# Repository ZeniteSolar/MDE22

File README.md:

# Electric Steering for Solar Boat

Instituto Federal de Educação, Ciência e Tecnologia de Santa Catarina - Campus Florianópolis

Electronics Academic Department

Degree in Electronics Engineering

Course: Integrative Project III

Professors:

* Robinson Pizzio and Daniel Lohmann

Student:

* Gabriel Ayres Rodrigues

# Summary

1. [Introduction](#introduction)
2. [Conception](#conception)
3. [Design](#design)
4. [Implementation](#implementation)
5. [Operation](#operation)
6. [Considerations](#considerations)
7. [References](#references)

# Introduction

This module aims to control the direction of the tail of the Guarapuvu II vessel, belonging to the IFSC Zênite Solar team.

It is inspired by the previously implemented system, developed by Cesar Dias Parente. The project files can be found [here](https://github.com/ZeniteSolar/MDE18/tree/main).

The Zênite team vessel is operated in solar boat competitions, where high performance and robustness are required. Being the only boat to use electric steering on the competition's context, the team counts on a more reliable system and is able to outmaneuver competition, which is a significant advantage on the Slalom race

The current electronic system was damaged after the competition in March 2022, which is a motivator for its upgrade.

# Conception

Thinking about a steering system, choosing to use an electric steering can bring greater responsiveness even though it has a fraction of the weight of a mechanical system. In addition, mechanical systems can require physical effort from the driver and a greater need for maintenance. 

Below is the diagram representing an electric steering system and its parts.

Taking into account the above elements, the following problems must be confronted:
- Electronic systems in vehicles must have high robustness due to the vibrations to which they are exposed. In the case of high speed vessels, especially for marine operations, impacts are a big problem (besides oxidation of the circuits).
- As the target vehicle is used in competitions whose focus, and therefore the challenge, is on energy generation and consumption, the solution must be as efficient as possible to ensure the success of the team.
- A competitive environment between vehicles requires high performance from this equipment, not only to achieve victory but to ensure everyone's safety. Therefore, the functionality must be met as well as the other parameters.

To implement the whole, it is necessary to define the requirements of the parts, and the possible proposals to satisfy them.

* ## Sensors

There are some options for rotation sensors such as: inductive, optical, Hall effect sensor, rotation potentiometer, encoder. The most economical and simple-to-implement alternative is a common linear potentiometer, currently used in the Zênite team system.

The most used types for steering sensors on the market are the following: resistive, encoders, and those with GMR technology ([Giant magnetoresistance](https://en.wikipedia.org/wiki/Giant_magnetoresistance)). (see the companies considered in [References](#references))

Sensors of this level are state-of-the-art and therefore out of the question, however it is worth noting that the resistive sensor is still being used (even in common vehicles, such as the [butterfly position sensor](https://www.dpk.com.br/como-funciona-o-sensor-de-posicao-da-borboleta/)).

For a contrast between the leaders: resistive sensors have a disadvantage due to wear and possible poor contact, GMR can suffer interference in environments with a strong magnetic field, and encoders (because they are digital) present a challenge in the trade-off Precision X Complexity (thus, price).

Seeking the balance between robustness, ease of implementation and price, the resistive sensor stands out.
 
* ## Controller

The implemented CAN network eliminates the need for cabling with analog signal between the stern and the bow. This ensures noise reduction in sensor readings and takes advantage of existing CAN cabling, compacting the system.

In addition, communication over the network makes it possible for the module to send data and control the direction using messages from other modules. In this way, the range is open for future implementations that may include:

	Redundancy messages and/or sensors
	Low Power Mode - Enabled by the Data Processing Module
	remote steering

A commercial line microcontroller will be enough to guarantee the execution of the desired tasks and response time. In addition to PWM ports and ADC inputs, a microcontroller with a CAN interface like the STM32F103xx or equivalent would be interesting. However, this alternative exceeds the price of IC's transceiver and CAN interface, in addition its programming is more laborious.

Due to its ease of programming and price, the [ATmega328P](https://br.mouser.com/ProductDetail/Microchip-Technology-Atmel/ATMEGA328P-PU?qs=K8BHR703ZXguOQv3sKbWcg%3D%3D) is proposed. For the connection to the CAN network, the most common and affordable IC's are the transceiver
[MCP2551](https://br.mouser.com/datasheet/2/268/20001667G-1115479.pdf) and the CAN/SPI interface circuit [MCP2515](https://br.mouser.com/datasheet/ 2/268/MCP2515_Family_Data_Sheet_DS20001801K-2303489.pdf).

The steering wheel potentiometer reading function will be performed by another module already present in the bow: [MIC19](https://github.com/ZeniteSolar/MIC19)

* ## Power Circuit

The brushed DC motor is driven by an H bridge, currently powered by a 12V battery. The current circuit is implemented by two half-bridge integrated [BTS7960](https://pdf1.alldatasheet.com/datasheet-pdf/view/152657/INFINEON/BTS7960.html).

This component was discontinued, and the best alternative found was [FAN7093](https://www.mouser.com/datasheet/2/149/FAN7093-76982.pdf). As the current one is already in hand and this project is focused on integration and telemetry, the same integrated circuit was used.

* ## Measurements and Feedback

It is essential to provide the CAN network with data on power consumption, as it is a battery-powered power system. Therefore, a current sensor is proposed for each arm of the H-bridge.

Conveniently, the BTS7960 half-bridge integrated circuit has an output pin for current sensing — a current source is connected to the output, and the current IS is proportional to the load current IL according to the measuring resistor RIS.

Alternatively, a circuit like the [INA240](https://www.ti.com/lit/ds/symlink/ina240.pdf?ts=1649772128538) ultra-precise bidirectional current sensor with PWM rejection could be used. From the same family of IC's, the INA826 will be used to measure battery voltage (Hbridge voltage).

These measurements should contribute to the feedback, which will also have the tail position data. Bringing this data to a display ensures that the pilot is aware of the state of the system and the consumption that his riding is causing.

# Design

The module was developed with Kicad software, the project is in the hardware folder of this git and its complete schematic can be viewed [here](https://github.com/ayresgit/Modulo-Direcao-Eletrica/blob/main/hardware/ PDF/steeringmodule.pdf). Below is the general schematic:

The components chosen from the design analysis are the following: Linear Potentiometers, Atmega328P, BTS7960, MCP2515, MCP2551 (or MCP2561), and INA826.

To conform to the vessel's system modules, the following components will also be required:

	2 female RJ45 connectors,
	2 2-way 2EDGRC female terminal (robust and practical, alternative is to use terminal block),
	28-pin stamped socket for the atmega328p,
	zener diodes to protect the microcontroller's ADC,
	2 oscillator crystals

The Kicad software has a function to export a complete list of materials (BOM - Bill Of Materials). It can be found in the hardware folder, at this [link](https://github.com/ZeniteSolar/MDE22/blob/f59e0732b5ff4f93045a860adb85f9820dcc4e83/hardware/steeringmodule.csv).

Right ahead is the PCB 3D preview. As will be explained in the implementation stage, the PCB was made with the help of a milling machine from the institution.

| Front | Back |
| -----  | ----- |
|||

It is worth noting that this repository has an exclusive branch for an ordered board, whose layout was improved and the silkscreen was properly designed to assist in the Implementation stage and possible repairs. This board was not used during the project due to its delivery date.

| Ordered Front | Ordered Back |
| -----  | ----- |
|||

# Implementation

### PCB manufacturing

The PCB was made by DAELN's CNC milling machine, operated by the department's technicians, the result is shown below. As the manufactured PCB did not have the desired minimum spacing for the power grid, a grinder was used to exclude unwanted tracks — it is important to remember that this type of tool requires the use of PPE.

| Dremel Adjustments | PPE |
| --- | --- |
||

The board was tinned to protect the circuit against oxidation, and the pathways were made with wires from network cable, cut to size and then soldered in place.

From the order of the components, the soldering was done as follows: SMD, CI, Through-hole connectors being the last ones (to avoid physical stress on the board).

After work on the board, the conclusion was reached that the H-bridge ICs must come before the SMD. This change is interesting because the model needs to be welded with heat, in this case with the aid of a heat gun. The soldered PCB can be seen in the figure.

| Front | Back |
|:-----:|:-----:|
|||

Once the preparation processes are finished, the microcontroller programming begins, which is done in the C language. The libraries used and the source code can be found in the firmware folder of this repository.

# Operation

The operation stage is divided into two parts: Programming and bench tests. Starting with the basic logic, such as which microcontroller peripherals are used, these steps develop together.

#### Programming

Throughout the process, the microchip datasheet for the atmega328p was used as a reference, which can be found in the [References](#references) of this work.

In the configuration of the peripherals, starting with the ADC, a dilemma was found about the orientation of the system potentiometers. As the system is being upgraded, the current configuration was discarded. It is then defined that the developed code presupposes the following relationships:

| Potentiometer | Tail position |
| ------------- | ------------------- |
| Maximum value | starboard boundary |
| Average value | centered |
| Minimum value | port limit |

- ADC

The mechanical system that couples the DC motor to the rotation reading potentiometer has a limit close to 270°. The ability to maneuver over 90° to either side has proven useful in the past.
With that in mind, and considering that extreme precision is not required in controlling this angle, the 8-bit ADC is sufficient for all four channels:

- voltage sensor
- current sensor 1 and 2
- Rotation sensor

Each one is configured by the coefficients in adc.c, just operate some measures with unitary coefficients and then do the calculation.

$$ coefficient = {DesiredValue \over ObtainedValue} $$
    
It is interesting to do this test with the full scale value, as the "Desired Value" is naturally known.

- CAN network

Working with the CAN library: the CAN network is implemented from ID's, identifying the modules on the bus and their messages. To generate these IDs, the Zênite team developed a script that generates these values for the module under development.

This path also brings security, ensuring that there will be no equal identities or other conflicts caused by human error and/or parallel development. All of these can be found in the [CAN_IDS](https://github.com/ZeniteSolar/CAN_IDS) repository.

Having the ID's generated for the module and its messages, it is necessary to change the can_filter.h to include the ID's of who you want to listen to (in this case, this project needs to listen to [MIC19](https://github.com/ZeniteSolar/MIC19 )), and create the request and message sending functions in can_app.c/h.

- PWM

Some key points for PWM operation: Chosen timer, prescaler (desired frequency), duty cycle definition (in this case implemented by the set_pwm function in hbridge.c).

Due to an error in the Design stage, the PWM outputs are connected to the ATmega328P's basic timer pins, Timer/Counter 0. The timer's operating mode must be phase correct PWM (which guarantees greater synchronization in relation to Fast PWM). As described in the datasheet, the frequency can be calculated as follows:

$$ fOCnxPWM = {fclkI/O \over {N * 510}} $$

	fOCnxPWM is the PWM frequency on the OCnx ports (in the case of OC0A and OC0B, in PD5 and PD6)
	fclkI/O is the crystal oscillator clock frequency (16MHz)
	N is the configured prescaler

This timer has fewer bits and less functionality compared to the other two. For the application, the only impact was the use of a lower frequency than desired (~3921.5Hz). This happens due to the lack of prescaler options in Timer/Counter0:
    
	prescaler = 1, fPWM = 31.37kHz (exceeds half-bridge IC limits)
	prescaler = 8 --> 3.92kHz (used, suboptimal)

#### Circuit Tests

The bench tests were carried out with the aid of different voltage sources, in the laboratories of the IFSC campus Florianópolis.

<p align="center">

The ADC and CAN network tests were carried out, these results were displayed on the computer by serial communication connecting an arduino to the board's Usart bus.

In the case of PWM, it is necessary to use an oscilloscope, so the figures for some of the tests carried out with the aid of a rheostat are left.

| Duty Cycle 40% Signal | Duty Cycle 40% Values |
| ------ | ------ |
|||

| Duty Cycle 80% | Duty Cycle 80% Values |
| ------ | ------ |
|||

To test the circuit with high current, the resistance in the rheostat was reduced and the duty cycle was maintained:
| Duty Cycle 80% 3A  | Duty Cycle 80% Valores |
| ------ | ------ |
|||

These results were satisfactory, considering that the circuit was not accumulating heat, the PWM was in accordance with what was desired from the configuration, and the values according to the datasheet.

#### Tests with Engine

The next step is the engine test. Bench test setup is done on the vessel, with bench supplies, boards and necessary connections.

<p align="center">

During the motor test, operating logics were implemented to the PWM of the H-bridge:

	H bridge activated by the difference between the potentiometers
	centered start
	Forced center if there is no communication
	Reverse side protection

The last logic was considered interesting considering that the system itself is assembled/disassembled for trips to competitions or testing sites.

The mechanical part can be seen in the figure below. The transmission shaft is coupled to the belt by the disc, and the DC steering motor controls the belt.
At the top of this can be seen the potentiometer used to measure rotation.

<p align="center">

The engine tests were a success using the bench sources, the operation video is in the Images folder. Due to the file size github cannot run it so it needs to be downloaded. An alternative is to use this [drive link](https://drive.google.com/file/d/12XCSZ1QREOxFkqlZAvMiaMpx_ZMUlxNi/view?usp=sharing).

During the test powered by the 12V battery, the system stopped working. The lack of capacitance for the input voltage caused a failure in one of the half-bridge ICs, after replacing the IC and correcting the values in the schematic the system is safe and operational.

# Considerations

All microcontroller peripherals are functional. All electrical measurements, which were one of the main objectives, showed satisfactory accuracy.

The essential logic of operation is complete, there are safety locks and finally the engine can be controlled smoothly.

Component performance: satisfactory.

Plate manufacturing: poor result, manufacturing caused more work and compromised the robustness of the system. To correctly meet the objective of a more robust system, the PCB ordered must be used.

Below we can see the system assembled with an experimental support — due to the dimensions of the board, a support dedicated to it needs to be manufactured.

On the side, the main power supply module ([MFP19](https://github.com/ZeniteSolar/MFP19)) is shown, which converts the voltage in the battery bank and supplies 18V from the CAN network. Future boat supports are expected to follow this 3D-printed model.

| Assembled System | Support Example |
| --- | --- |
|||

For comparison, here are screenshots of the previous system.

| Previous System | H Bridge |
| --- | --- |
|||

#### Next steps

Some of the next steps for this module and future updates:

- PWM responsive to pilot movements
- H-Bridge design or choice of non-discontinued IC
- Redundancy messages and/or sensors
- Low power mode - Activated by data processing module
- *Remote steering

*The success of this step would make room for a fascinating update: The Autonomous Boat.

# References

Datasheet ATmega328P:
[Microchip, Atmel ATmega328P](https://ww1.microchip.com/downloads/en/DeviceDoc/Atmel-7810-Automotive-Microcontrollers-ATmega328P_Datasheet.pdf)

Steering sensor market research:
[Bosch](https://www.bosch-motorsport.com/content/downloads/Raceparts/en-GB/120530059.html),
[CUI Inc](https://www.cuidevices.com/catalog/motion/rotary-encoders),
[TT Electronics](https://www.ttelectronics.com/products/categories/steering-sensors/search-results/)

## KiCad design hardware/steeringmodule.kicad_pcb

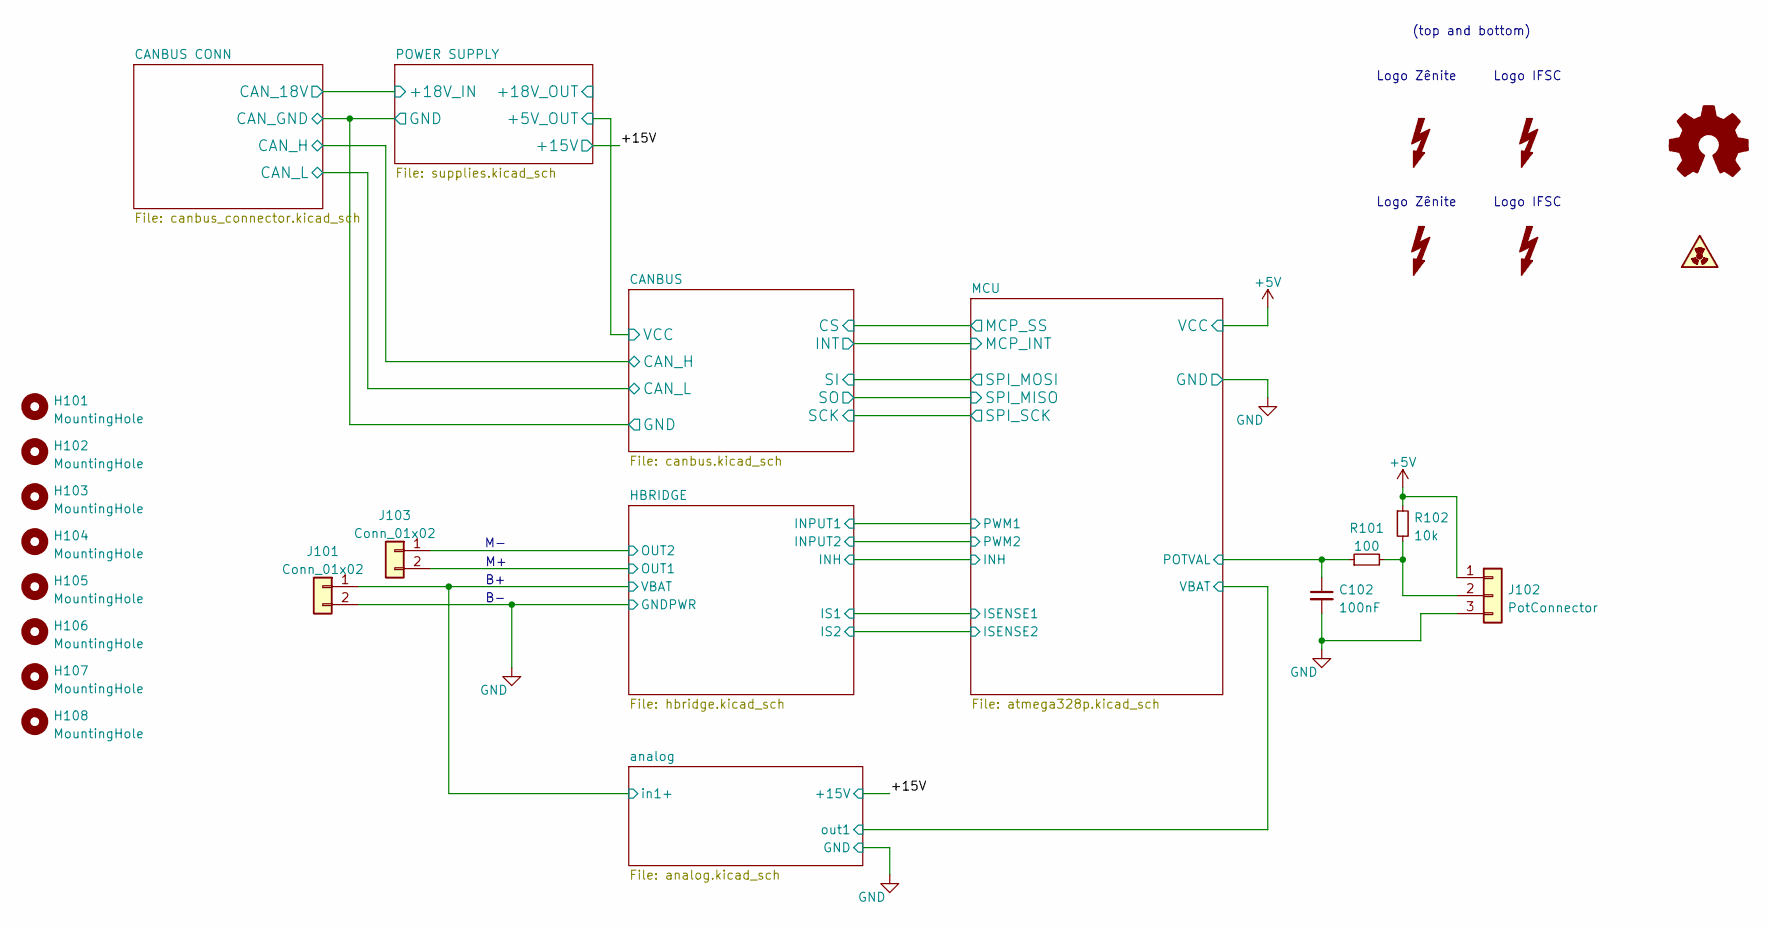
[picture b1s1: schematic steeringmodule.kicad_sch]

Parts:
C102: 100nF; C_0805_2012Metric_Pad1.18x1.45mm_HandSolder
H101, H102, H103, H104, H105, H106, H107, H108: MountingHole; MountingHole_3.2mm_M3
J101, J103: Conn_01x02; PhoenixContact_MSTBA_2,5_2-G-5,08_1x02_P5.08mm_Horizontal
J102: PotConnector; PhoenixContact_MSTBA_2,5_3-G-5,08_1x03_P5.08mm_Horizontal
LOGO101: Logo_Open_Hardware_Small; OSHW-Logo2_7.3x6mm_SilkScreen
R101: 100; R_0805_2012Metric_Pad1.20x1.40mm_HandSolder
R102: 10k; R_0805_2012Metric_Pad1.20x1.40mm_HandSolder
SYM101, SYM102: SYM_Flash_Small; symbol_logoZenite
SYM103, SYM104: SYM_Flash_Small; synbol_logoifsc
SYM105: SYM_Radioactive_Radiation_Small; symbol_naolavar

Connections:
/HBRIDGE/OUT1: J103.2; also elsewhere on the board
/HBRIDGE/OUT2: J103.1; also elsewhere on the board
/HBRIDGE/VS1: J101.1; also elsewhere on the board
/MCU/POTVAL: C102.1, R101.1; also elsewhere on the board
unnamed: J102.2, R101.2, R102.2

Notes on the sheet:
Logo Zênite
(top and bottom)
Logo IFSC

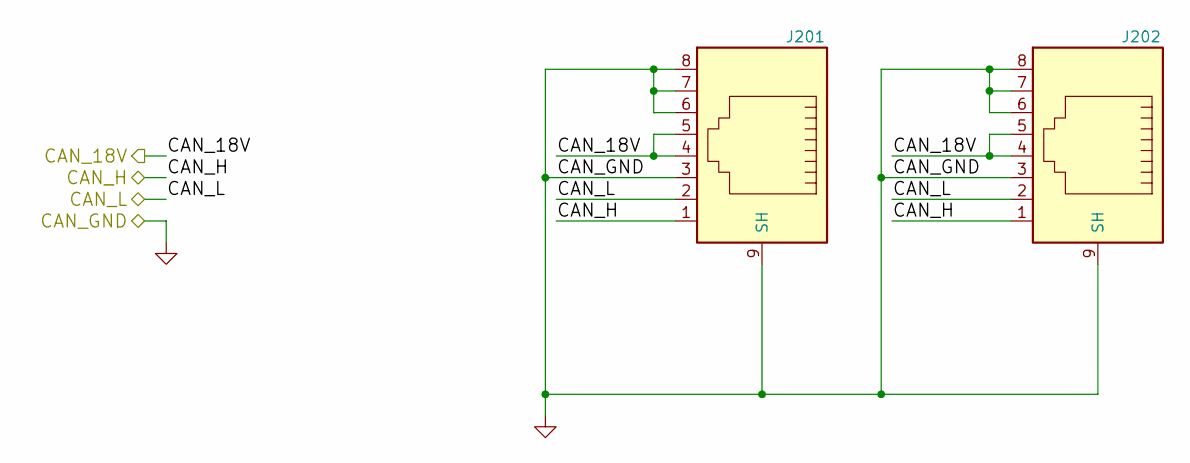
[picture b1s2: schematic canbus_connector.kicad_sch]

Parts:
J201, J202: RJ45_YH59_01

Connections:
/CANBUS CONN/CAN_18V: J201.4, J201.5, J202.4, J202.5; also elsewhere on the board
/CANBUS CONN/CAN_H: J201.1, J202.1; also elsewhere on the board
/CANBUS CONN/CAN_L: J201.2, J202.2; also elsewhere on the board

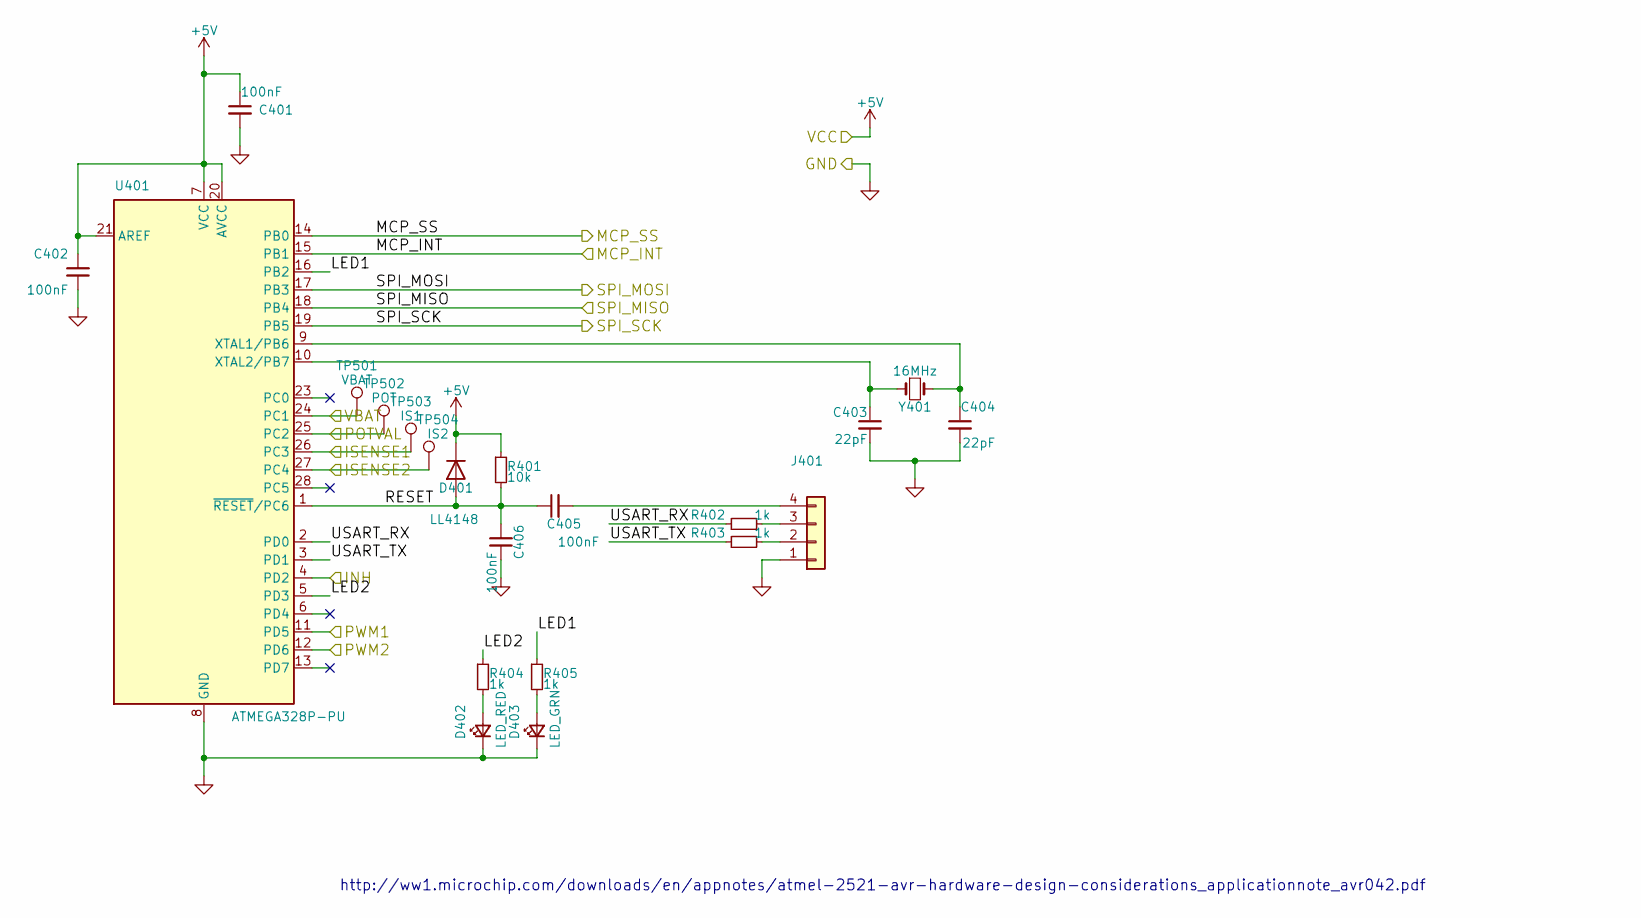
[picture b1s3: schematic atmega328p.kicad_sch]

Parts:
C401, C402, C405, C406: 100nF; C_0805_2012Metric_Pad1.18x1.45mm_HandSolder
C403, C404: 22pF; C_0805_2012Metric_Pad1.18x1.45mm_HandSolder
D401: LL4148; D_MiniMELF
D402: LED_RED; LED_0805_2012Metric_Pad1.15x1.40mm_HandSolder
D403: LED_GRN; LED_0805_2012Metric_Pad1.15x1.40mm_HandSolder
J401: PinHeader_1x04_P2.54mm_Vertical
R401: 10k; R_0805_2012Metric_Pad1.20x1.40mm_HandSolder
R402, R403, R404, R405: 1k; R_0805_2012Metric_Pad1.20x1.40mm_HandSolder
TP501: VBAT; TestPoint_Pad_2.0x2.0mm
TP502: POT; TestPoint_Pad_2.0x2.0mm
TP503: IS1; TestPoint_Pad_2.0x2.0mm
TP504: IS2; TestPoint_Pad_2.0x2.0mm
U401: ATMEGA328P-PU; DIP-28_W7.62mm_Socket
Y401: 16MHz; Crystal_HC49-U_Vertical

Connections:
/HBRIDGE/INH: U401.4 (PD2); also elsewhere on the board
/HBRIDGE/INPUT1: U401.11 (PD5); also elsewhere on the board
/HBRIDGE/INPUT2: U401.12 (PD6); also elsewhere on the board
/HBRIDGE/IS1: TP503.1, U401.26 (PC3); also elsewhere on the board
/HBRIDGE/IS2: TP504.1, U401.27 (PC4); also elsewhere on the board
/MCU/LED1: R405.1, U401.16 (PB2)
/MCU/LED2: R404.1, U401.5 (PD3)
/MCU/MCP_INT: U401.15 (PB1); also elsewhere on the board
/MCU/MCP_SS: U401.14 (PB0); also elsewhere on the board
/MCU/POTVAL: TP502.1, U401.25 (PC2); also elsewhere on the board
/MCU/RESET: C405.1, C406.2, D401.2 (A), R401.2, U401.1 (~RESET/PC6)
/MCU/SPI_MISO: U401.18 (PB4); also elsewhere on the board
/MCU/SPI_MOSI: U401.17 (PB3); also elsewhere on the board
/MCU/SPI_SCK: U401.19 (PB5); also elsewhere on the board
/MCU/USART_RX: R402.1, U401.2 (PD0)
/MCU/USART_TX: R403.1, U401.3 (PD1)
/MCU/VBAT: TP501.1, U401.24 (PC1); also elsewhere on the board
unnamed: C403.1, U401.10 (XTAL2/PB7), Y401.1
unnamed: C404.1, U401.9 (XTAL1/PB6), Y401.2
unnamed: C405.2, J401.4
unnamed: D402.2 (A), R404.2
unnamed: D403.2 (A), R405.2
unnamed: J401.2, R403.2
unnamed: J401.3, R402.2

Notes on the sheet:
http://ww1.microchip.com/downloads/en/appnotes/atmel-2521-avr-hardware-design-considerations_applicationnote_avr042.pdf

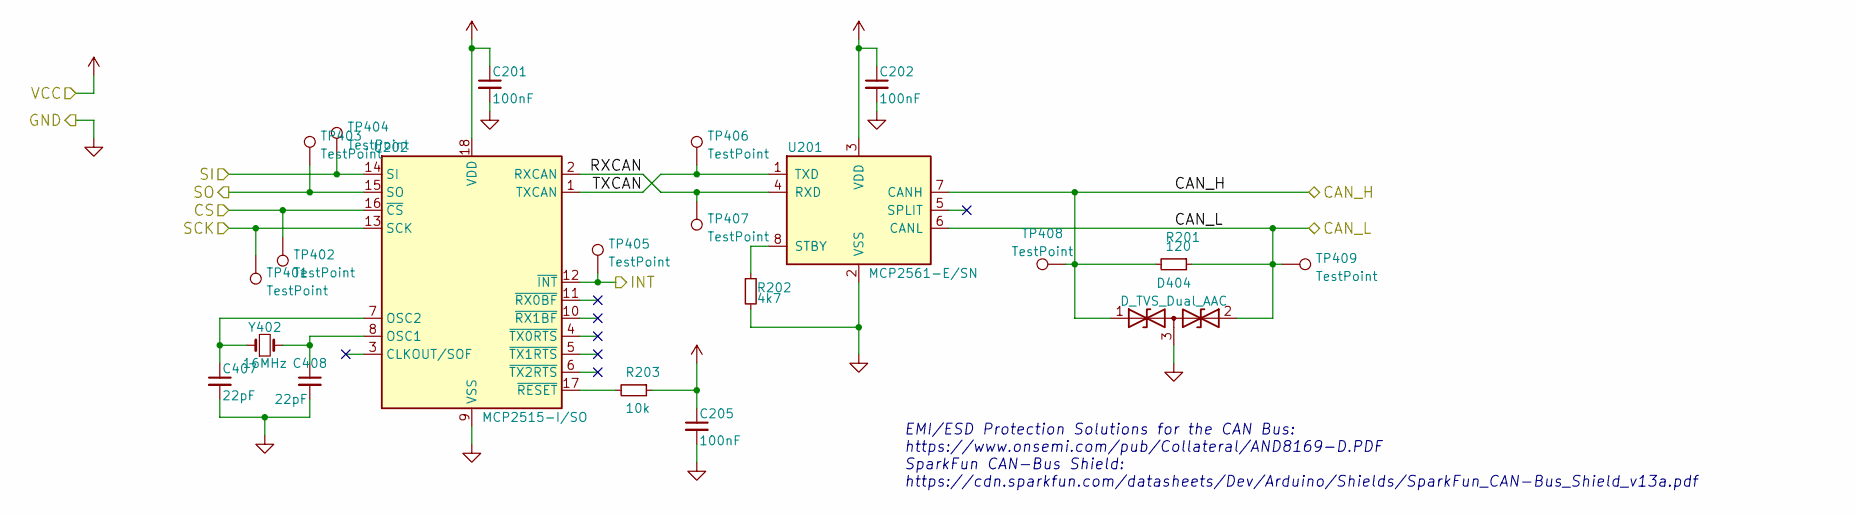
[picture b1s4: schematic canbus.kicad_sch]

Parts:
C201, C202, C205: 100nF; C_0805_2012Metric_Pad1.18x1.45mm_HandSolder
C407, C408: 22pF; C_0805_2012Metric_Pad1.18x1.45mm_HandSolder
D404: D_TVS_Dual_AAC; SOT-23
R201: 120; R_0805_2012Metric_Pad1.20x1.40mm_HandSolder
R202: 4k7; R_0805_2012Metric_Pad1.20x1.40mm_HandSolder
R203: 10k; R_0805_2012Metric_Pad1.20x1.40mm_HandSolder
TP401, TP402, TP403, TP404, TP405, TP406, TP407, TP408, TP409: TestPoint; TestPoint_Pad_2.0x2.0mm
U201: MCP2561-E/SN; SO-8_3.9x4.9mm_P1.27mm
U202: MCP2515-I/SO; SOIC-18W_7.5x11.6mm_P1.27mm
Y402: 16MHz; Crystal_HC49-U_Vertical

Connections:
/CANBUS CONN/CAN_H: D404.1 (A1), R201.2, TP408.1, U201.7 (CANH); also elsewhere on the board
/CANBUS CONN/CAN_L: D404.2 (A2), R201.1, TP409.1, U201.6 (CANL); also elsewhere on the board
/CANBUS/RXCAN: TP407.1, U201.4 (RXD), U202.2 (RXCAN)
/CANBUS/TXCAN: TP406.1, U201.1 (TXD), U202.1 (TXCAN)
/MCU/MCP_INT: TP405.1, U202.12 (~INT); also elsewhere on the board
/MCU/MCP_SS: TP402.1, U202.16 (~CS); also elsewhere on the board
/MCU/SPI_MISO: TP403.1, U202.15 (SO); also elsewhere on the board
/MCU/SPI_MOSI: TP404.1, U202.14 (SI); also elsewhere on the board
/MCU/SPI_SCK: TP401.1, U202.13 (SCK); also elsewhere on the board
unnamed: C407.1, U202.7 (OSC2), Y402.1
unnamed: C408.1, U202.8 (OSC1), Y402.2
unnamed: R202.1, U201.8 (STBY)
unnamed: R203.2, U202.17 (~RESET)

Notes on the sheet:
EMI/ESD Protection Solutions for the CAN Bus: https://www.onsemi.com/pub/Collateral/AND8169-D.PDF SparkFun CAN-Bus Shield: https://cdn.sparkfun.com/datasheets/Dev/Arduino/Shields/SparkFun_CAN-Bus_Shield_v13a.pdf

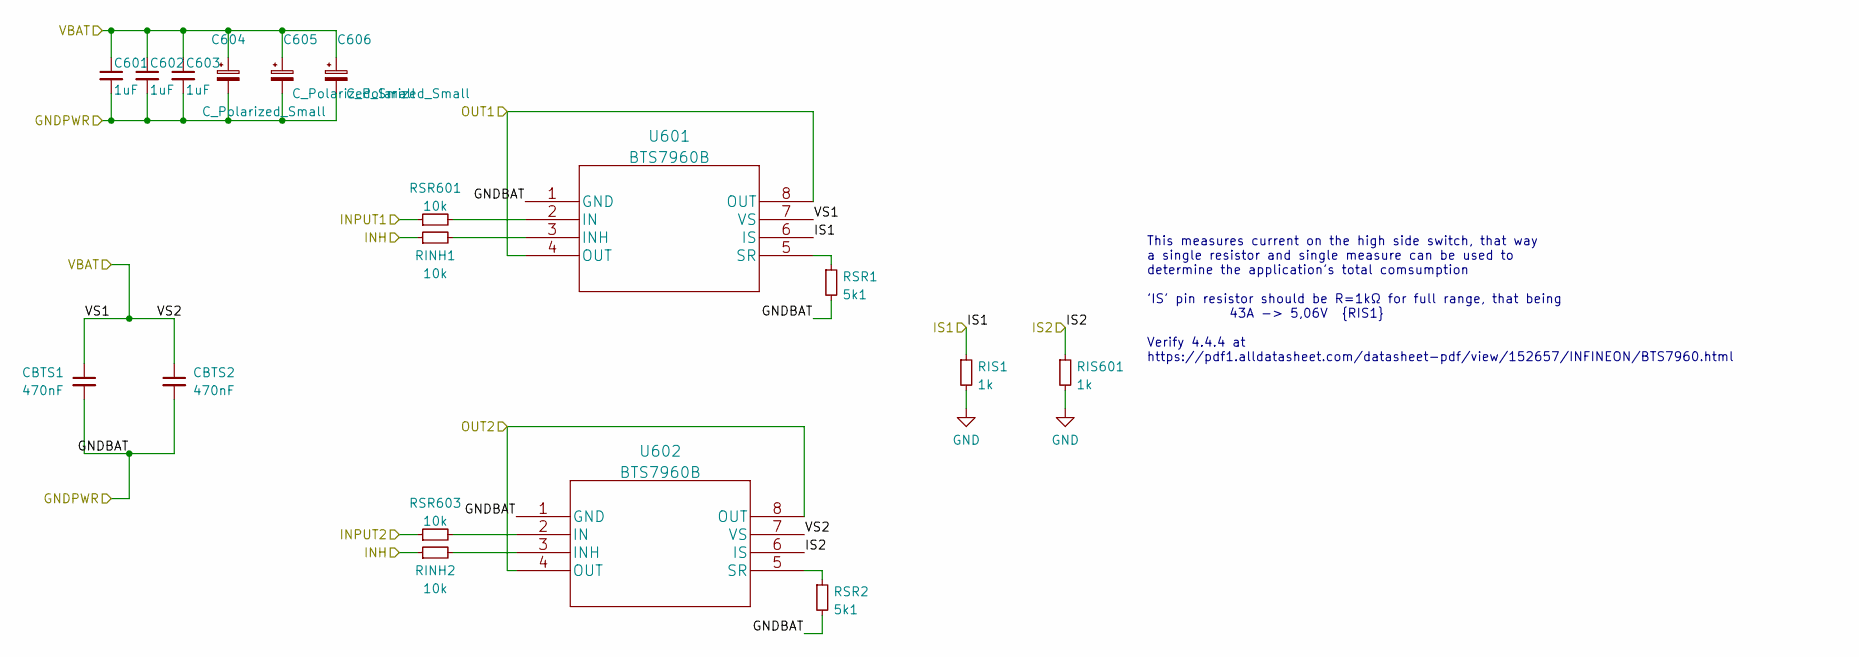
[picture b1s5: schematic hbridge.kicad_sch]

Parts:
C601, C602, C603: 1uF; C_1206_3216Metric_Pad1.33x1.80mm_HandSolder
C604, C605, C606: C_Polarized_Small; CP_Elec_8x10
CBTS1, CBTS2: 470nF; C_0805_2012Metric_Pad1.18x1.45mm_HandSolder
RINH1, RINH2: 10k; R_0805_2012Metric_Pad1.20x1.40mm_HandSolder
RIS1, RIS601: 1k; R_0805_2012Metric_Pad1.20x1.40mm_HandSolder
RSR1, RSR2: 5k1; R_0805_2012Metric_Pad1.20x1.40mm_HandSolder
RSR601, RSR603: 10k; R_0805_2012Metric_Pad1.20x1.40mm_HandSolder
U601, U602: BTS7960B; TO-263-7_TabPin8

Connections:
/HBRIDGE/INH: RINH1.1, RINH2.1; also elsewhere on the board
/HBRIDGE/INPUT1: RSR601.1; also elsewhere on the board
/HBRIDGE/INPUT2: RSR603.1; also elsewhere on the board
/HBRIDGE/IS1: RIS1.1, U601.6 (IS); also elsewhere on the board
/HBRIDGE/IS2: RIS601.1, U602.6 (IS); also elsewhere on the board
/HBRIDGE/OUT1: U601.4 (OUT), U601.8 (OUT); also elsewhere on the board
/HBRIDGE/OUT2: U602.4 (OUT), U602.8 (OUT); also elsewhere on the board
/HBRIDGE/VS1: C601.1, C602.1, C603.1, C604.1, C605.1, C606.1, CBTS1.1, CBTS2.1, U601.7 (VS), U602.7 (VS); also elsewhere on the board
unnamed: RINH1.2, U601.3 (INH)
unnamed: RINH2.2, U602.3 (INH)
unnamed: RSR1.1, U601.5 (SR)
unnamed: RSR2.1, U602.5 (SR)
unnamed: RSR601.2, U601.2 (IN)
unnamed: RSR603.2, U602.2 (IN)

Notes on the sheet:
This measures current on the high side switch, that way a single resistor and single measure can be used to determine the application's total comsumption 'IS' pin resistor should be R=1kΩ for full range, that being 43A -> 5,06V {RIS1} Verify 4.4.4 at https://pdf1.alldatasheet.com/datasheet-pdf/view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

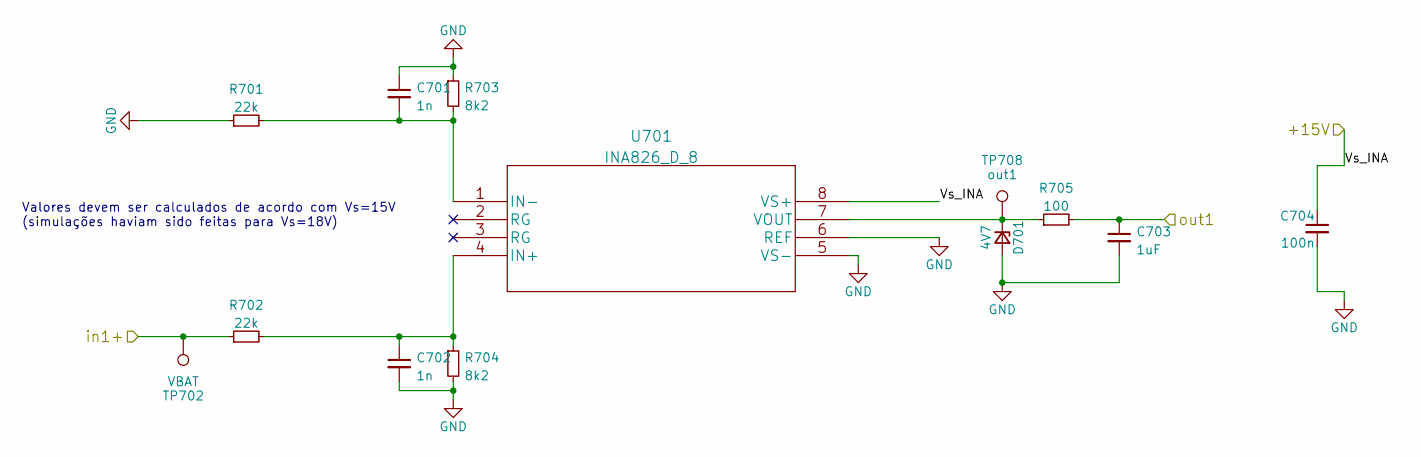
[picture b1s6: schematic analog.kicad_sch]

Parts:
C701, C702: 1n; C_0805_2012Metric_Pad1.18x1.45mm_HandSolder
C703: 1uF; C_1206_3216Metric_Pad1.33x1.80mm_HandSolder
C704: 100n; C_0805_2012Metric_Pad1.18x1.45mm_HandSolder
D701: 4V7; D_MiniMELF_Handsoldering
R701, R702: 22k; R_0805_2012Metric_Pad1.20x1.40mm_HandSolder
R703, R704: 8k2; R_0805_2012Metric_Pad1.20x1.40mm_HandSolder
R705: 100; R_0805_2012Metric_Pad1.20x1.40mm_HandSolder
TP702: VBAT; TestPoint_Pad_2.0x2.0mm
TP708: out1; TestPoint_Pad_2.0x2.0mm
U701: INA826_D_8; SOIC-8_3.9x4.9mm_P1.27mm

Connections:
/+15V: C704.1, U701.8 (VS+); also elsewhere on the board
/HBRIDGE/VS1: R702.1, TP702.1; also elsewhere on the board
/MCU/VBAT: C703.1, R705.2; also elsewhere on the board
unnamed: C701.2, R701.2, R703.2, U701.1 (IN-)
unnamed: C702.1, R702.2, R704.1, U701.4 (IN+)
unnamed: D701.1 (K), R705.1, TP708.1, U701.7 (VOUT)

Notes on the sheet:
Valores devem ser calculados de acordo com Vs=15V (simulações haviam sido feitas para Vs=18V)

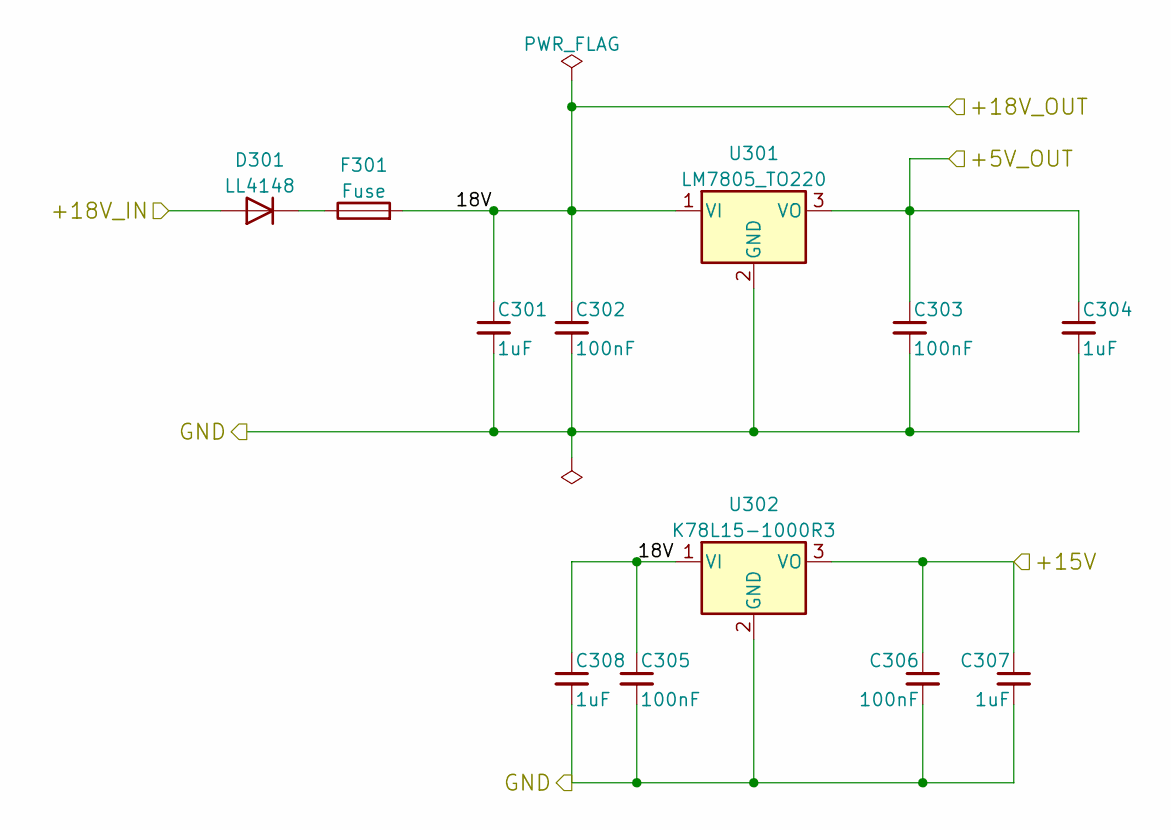
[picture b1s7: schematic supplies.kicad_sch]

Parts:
C301, C304, C307, C308: 1uF; C_1206_3216Metric_Pad1.33x1.80mm_HandSolder
C302, C303, C305, C306: 100nF; C_0805_2012Metric_Pad1.18x1.45mm_HandSolder
D301: LL4148; D_MiniMELF
F301: Fuse; Fuse_1206_3216Metric_Pad1.42x1.75mm_HandSolder
U301: LM7805_TO220; TO-220-3_Horizontal_TabDown_SMD
U302: K78L15-1000R3; TO-220-3_Horizontal_TabDown_SMD

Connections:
/+15V: C306.1, C307.1, U302.3 (VO); also elsewhere on the board
/CANBUS CONN/CAN_18V: D301.2 (A); also elsewhere on the board
/POWER SUPPLY/18V: C301.1, C302.1, C305.1, C308.1, F301.2, U301.1 (VI), U302.1 (VI)
unnamed: D301.1 (K), F301.1

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
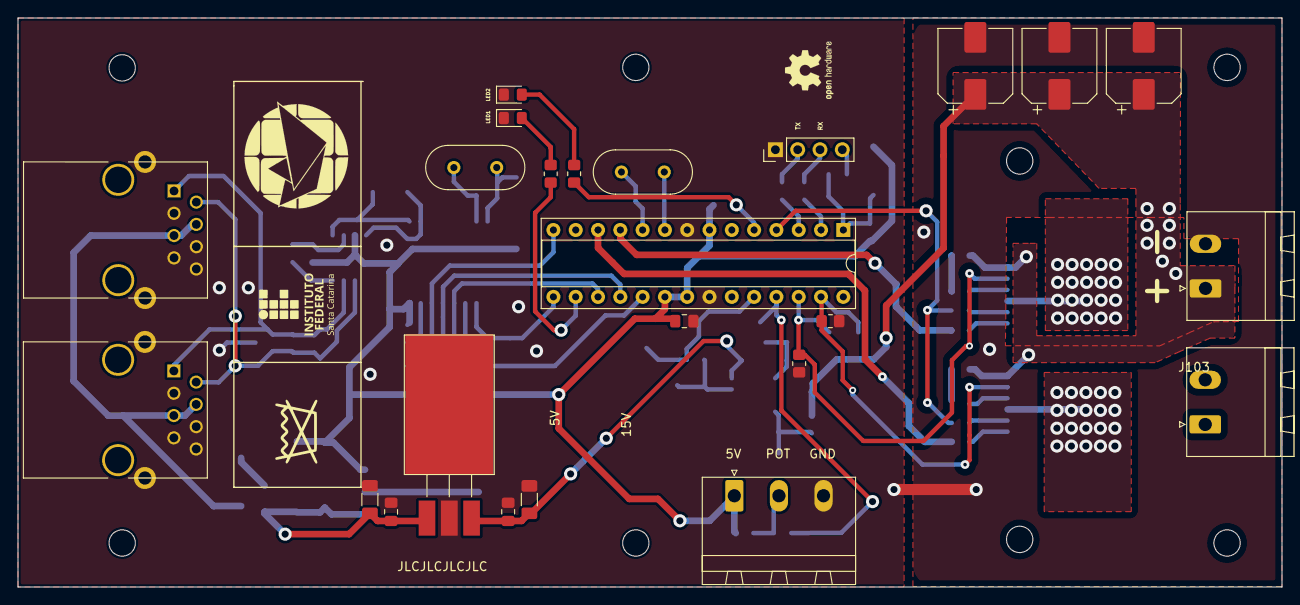
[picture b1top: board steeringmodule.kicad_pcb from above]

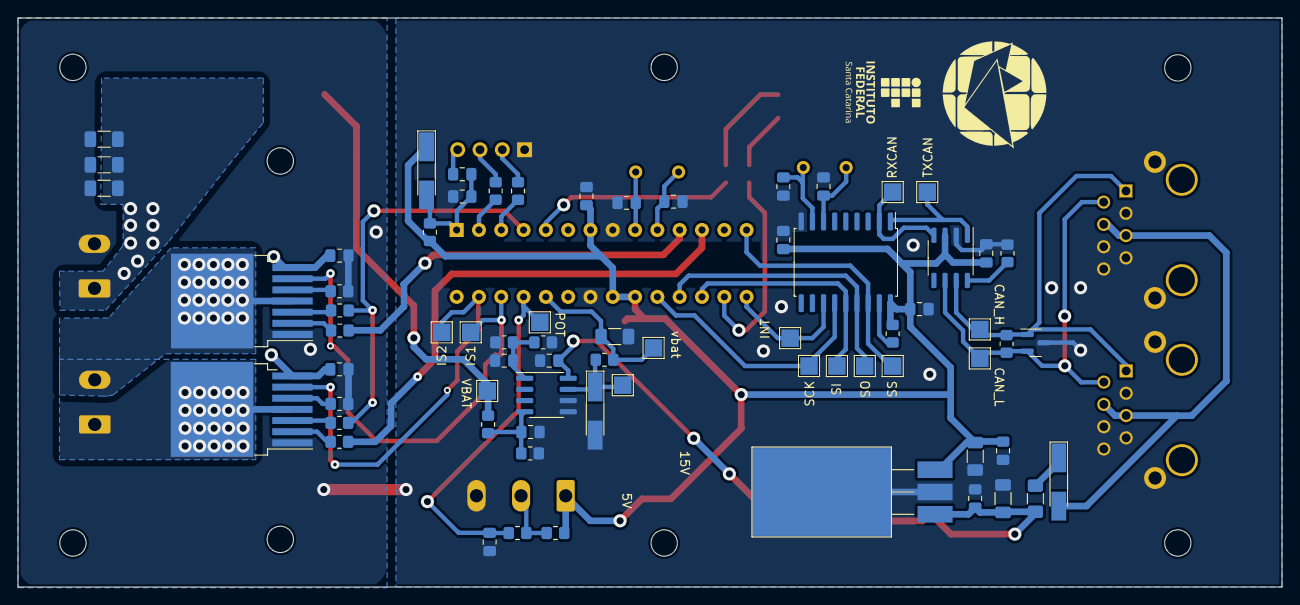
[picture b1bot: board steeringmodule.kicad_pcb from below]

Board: 2 copper layers, 144.0 x 64.8 mm, 107 parts (71 on the bottom side), 51 nets.

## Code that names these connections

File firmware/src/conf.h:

/**
 * @file conf.h
 *
 * @defgroup CONF Configurations
 *
 * @brief General configuration of the system.
 *
 */

#ifndef CONF_H
#define CONF_H
#ifndef F_CPU
#define F_CPU 16000000UL    //define a frequencia do microcontrolador - 16MHz
#endif /* ifndef F_CPU */


// CONFIGURACOES DE COMPILACAO
//#define DEBUG_ON
#define VERBOSE_ON
//#define VERBOSE_ON_CAN_APP
#define VERBOSE_ON_MACHINE
#define VERBOSE_ON_ADC
#define VERBOSE_ON_INIT
#define PRINT_INFOS
//#define VERBOSE_ON_ERROR
//#define VERBOSE_ON_HBRIDGE

// MODULES ACTIVATION
#define USART_ON
#define CAN_ON
//#define CAN_DEPENDENT
#define ADC_ON
#define MACHINE_ON
#define HBRIDGE_ON
#define LED_ON
#define WATCHDOG_ON
//#define SLEEP_ON
#define PRINT_INFOS

#define CAN_SIGNATURE_SELF                  CAN_SIGNATURE_MDE22



// The machine frequency may not be superior of ADC_FREQUENCY/ADC_AVG_SIZE_10
#ifdef MACHINE_ON
// The machine frequency may not be superior of ADC_FREQUENCY/ADC_AVG_SIZE_10
#define MACHINE_TIMER_FREQUENCY 120UL  //<! machine timer frequency in Hz
#define MACHINE_TIMER_PRESCALER 1024UL //<! machine timer prescaler
#define MACHINE_FREQUENCY MACHINE_TIMER_FREQUENCY
#endif // MACHINE_ON              (MACHINE_TIMER_FREQUENCY)/(MACHINE_CLK_DIVIDER_VALUE)

#ifdef  HBRIDGE_ON
//#define HBRIDGE_TIMER_FREQUENCY             0
//#define HBRIDGE_TIMER_PRESCALER             0
//#define HBRIDGE_SWITCHING_FREQUENCY         0
#define HBRIDGE_CLK_DIVIDER_VALUE           (HBRIDGE_TIMER_FREQUENCY)/(HBRIDGE_SWITCHING_FREQUENCY)
#define HBRIDGE_PORT                        PORTD
#define HBRIDGE_PWM_DDR                     DDRD
#define HBRIDGE_PWM_PIN1                    PD6
#define HBRIDGE_PWM_PIN2                    PD5   
#define HBRIDGE_ENABLE_PIN                  PD2
#define HBRIDGE_VERBOSE_CLK_DIV             50
#define HBRIDG_SIDE_SWITCH_CLK_DIV          3000
#define TAIL_TOLERANCE                      7
#define H_MAX_RANGE                         1/255
#endif // HBRIDGE_ON

//#### LED PINS ####
#ifdef LED_ON
#define     LED1_PORT                   PORTD
#define     LED1_PIN                    PIND
#define     LED1_DDR                    DDRD
#define     LED1                        PD3

#define     LED2_PORT                   PORTB
#define     LED2_PIN                    PINB
#define     LED2_DDR                    DDRB
#define     LED2                        PB2

#else
#define     cpl_led()
#define     set_led()
#define     clr_led()
#endif // LED_ON


#ifdef CAN_ON
#define SPI_ON
#define CAN_APP_SEND_STATE_FREQ     (MACHINE_TIMER_FREQUENCY / CAN_MSG_MDE22_STATE_FREQUENCY)
#define CAN_APP_SEND_ADC_FREQ       (MACHINE_TIMER_FREQUENCY / CAN_MSG_MDE22_STEERINGBAT_MEASUREMENTS_FREQUENCY)

// CANBUS DEFINITONS
// ----------------------------------------------------------------------------
/* Global settings for building the can-lib and application program.
 *
 * The following two #defines must be set identically for the can-lib and
 * your application program. They control the underlying CAN struct. If the
 * settings disagree, the underlying CAN struct will be broken, with
 * unpredictable results.
 * If can.h detects that any of the #defines is not defined, it will set them
 * to the default values shown here, so it is in your own interest to have a
 * consistent setting. Ommiting the #defines in both can-lib and application
 * program will apply the defaults in a consistent way too.
 *
 * Select if you want to use 29 bit identifiers.
 */
#define	SUPPORT_EXTENDED_CANID	0

/* Select if you want to use timestamps.
 * Timestamps are sourced from a register internal to the AT90CAN.
 * Selecting them on any other controller will have no effect, they will
 * be 0 all the time.
 */
#define	SUPPORT_TIMESTAMPS		0
#endif // CAN_ON

#endif /* ifndef CONF_H */

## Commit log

2022-05-03 Create delete
2022-06-08 hardware: Protótipo da PCB
2022-06-15 hardware: added 3D IMG archives and schematic PDF
2022-06-21 Added analog stage for Vbat measurement, and it's simulation
2022-06-21 Adjusted analog, now using INA826. Simulations updated.
2022-06-29 hardware: added shapes 3D
2022-07-01 hardware: K78L15 to supply INA826 and other changes
2022-07-01 hardware: silkscreen updated with JLC. Finished.
2022-07-14 added firmware directory
2022-07-15 Changed ADC timer0->timer1, added can msg measurements
2022-07-16 gitignore, fixed adc variables declaration errors
2022-07-18 Leds use different ports, defined now
2022-07-18 No longer using '_led' functions because of different ports
2022-07-18 Board on running state
2022-07-19 Running state, CAN_OFF
2022-07-19 Redefined registers for Timer/Counter1 Compare Match B
2022-07-19 Running state changes made for debug purposes
2022-07-19 Set SS pin
2022-07-19 Cleared task_running delays (duh)
2022-07-19 ADC Compares with OCIE1B, changed emprt int to timer1_compB
2022-07-19 Deleted aditional ADC frequency definitions
2022-07-19 Change to registers, ISR still not working
2022-07-19 Deleted VERBOSE for additional ADC config
2022-07-19 Reorganized and included ADC_PRESCALER to TCCR1B
2022-07-19 Fixed prescaler on 64 to test clock selection
2022-07-19 Variables are now uint16_t (previous uint8_t)
2022-07-19 ADC working properly. Usart messages removed.
2022-07-19 No fake adc
2022-07-19 Removed unused ADC variables. task_running contains usart msgs for adc troubleshooting.
2022-07-20 Added batvoltage coef, removed usart msgs
2022-07-20 Organization
2022-07-20 Compute and reset masurements on task_running
2022-07-20 adc variables are type float, vcoeff correct
2022-07-20 Usart send batcurrent added
2022-07-20 CAN ON, adc working properly (pot not linear)
2022-07-20 CAN is working, verbose activated
2022-07-20 batvolt and position coeffs adjusted
2022-07-20 no verbose
2022-07-20 Messages ON, led clk div altered for demo
2022-07-20 Disable loopback mode
2022-07-21 Changed from generic to MDE variables
2022-07-21 Verbose on can_app
2022-07-21 CAN_APP_SEND_FREQ restored
2022-07-21 Dummy forgot to change CAN_SIGNATURE_SELF, corrected
2022-07-21 Changed variables to generic
2022-07-21 ADC and CAN working
2022-07-22 Created H bridge modules, with init and testing functions
2022-07-22 Added HBRIDGE includes and functions
2022-07-23 Added stty for usart observation
2022-07-23 Add hbridge set pwm and related variables
2022-07-23 Working pwm, hbridge_set_pwm added
2022-07-24 Posiçlão dos potenciômetros explicada na Implementação
2022-07-24 Added HIGH_LOW, RISING_EDGE and FALLING_EDGE
2022-07-24 Changed mic17 names to mic19. Added mic19_mde extractor
2022-07-24 Include hbridge.h, change mic17 to mic19
2022-07-24 Defined VERBOSE_ON_HBRIDGE
2022-07-24 Removed unecessary declarations
2022-07-24 Full hbridge_task, added future speed control variables
2022-07-24 Add future speed control variables, includde usart
2022-07-25 Added error flags invalid_str_wheel and invalid_tail
2022-07-25 Define TAIL_TOLERANCE, hbridge_task checks for invalid positions (hard limits)
2022-07-25 Tail and steering wheel position is limited as 270
2022-07-25 Hbridge verbose clk div
2022-07-25 HBRIDGE_VERBOSE_CLK_DIV 400
2022-07-25 Running task no longer makes measurements
2022-07-25 Duty coeff = 0.1, verbose_clk_div added
2022-07-25 Define HBRIDGE_VERBOSE_CLK_DIV 120
2022-07-25 Receive MIC19 messages
2022-07-25 Checks without mic19
2022-07-26 Testing deleted, added tst_bit on enable bridge and error flag if angle>270
2022-07-26 Adjusted Vbat measurements coefficients
2022-07-26 Added tail tolerance and side_switch_clk_div (prototype)
2022-07-26 Added verbose on hbridge
2022-07-26 No longer takes measurements in running nor flips led
2022-07-26 hbridge_flags used for can independency (center tail if no MIC19 msgs)
2022-07-26 hbridge_flags, duty_coeff, and side_switch prototype
2022-07-26 Init on flag force_center, wrong side check, verbose msgs
2022-07-27 Documentation
2022-07-27 Reset dail diff if 0
2022-07-27 tail_diff_old = tail_diff in the end of task
2022-07-28 Atualização da operação
2022-07-28 Imagens para o README
2022-07-29 Correctec comment that was being executed
2022-07-29 Concepção adequadamente finalizada, design em processo
2022-07-29 Created BOM, removed Testpoints from it.
2022-07-29 Atualizando Implementação, Operação, Referências
2022-07-29 Correção de texto, hyperlink e imagens
2022-07-29 Corrigindo hyperlink
2022-07-29 Atualizando README
2022-07-29 Referências
2022-07-29 Atualizando Imagens
2022-07-29 Operação e Consideraçoes
2022-07-29 Vídeo do funcionamento
2022-07-29 Resize PCB image
2022-07-29 Update Imagens
2022-07-29 Considerações
2022-07-29 Imagens da placa encomendada
2022-07-29 Imagens da placa encomendada adicionadas ao README
2022-07-29 Redimensionando Imagens da placa encomendada
2022-07-29 Finalizando o README
2022-07-29 Renomeando o vídeo de funcionamento
2022-08-16 tail_position_pilot is now called str_whl_position
2022-08-16 wrong_side_turn is now on machine struct error_flags
2022-08-16 Documentation, organized hbridge_task error checks
2022-08-16 wrong_side_turn is an error flag, invalid_str_whl deleted
2022-08-16 If errors >= 2 reset_state will be set (wrong side or invalid tail angle)
2022-08-23 Start variable Duty Cycle tests
2022-09-06 Organized verbose messages
2022-09-08 Changed hbridge_verbose_clk_div
2022-09-08 Changed led_clk_div
2022-09-08 Succesfull variable duty cycle with tail__diff_old
2022-09-08 Chande TAIL_TOLERANCE from 3 to 2
2022-09-08 Organized 'if' statements in bridge operation, corrected documentation
2022-09-25 Reduced led_clk_div 50 -> 10
2022-09-25 Increased TAIL_TOLERANCE from 2 to 7, changed hbridge_verbose_clk_div from 50 to 10
2022-09-25 Created structure can_app_flags
2022-09-25 can_app acts on its own flags, no longer altering hbridge flags
2022-09-25 Binded safeguards for no_mic and str angle, force center shall act properly
2022-09-26 LED2 OFF if CAN OFF
2022-09-26 Better usart messages
2022-09-26 Verbose on hbridge
2022-09-26 no_mic_responde now called no_mic
2022-09-26 Corrected assignment of duty_coeff value, led1 blink freq changes according to force_center
2022-10-02 Usart send position, temporary remove of invalid_tail check
2022-10-02 Change coefficients to max angle 256, decrease led blink frequency if no_mic
2022-10-02 Change position_coeff so that max angle is 255
2022-10-02 Change position coeff
2022-10-02 ToDo: Fix batcurrent coefficient
2022-10-14 Fix syntax errors
2022-11-11 Can_app_send_'MSG'_freq updated according to new frequency plan
2022-11-11 Changed position variables from uint16 to uint8
2022-11-11 DEFINE macro for 1/255, used to determine duty_ccoeff
2022-11-11 LED2 with can_app_send_measurements frequency
2022-11-11 Changed idle and initializing led1 to led2
2022-11-11 Fixed duty_coeff error
2022-11-11 Changed definition of H_MAX_RANGE
2022-11-11 Control: implement PI controller
2022-11-11 control: PI tunning
2023-01-17 Update README, create english version
2023-01-17 Add Block Diagram
2023-05-29 update constants
2023-05-29 ident machine
2023-07-03 before lic changes
2023-08-04 Add comments and suggestions
2023-09-19 feat[control]: Improve control algorithm
2023-10-19 generate bom
2024-06-11 fix: fix atmega freezing when sending float via UART
2025-06-10 define print infos
2025-06-10 include math.h
2025-06-10 better print infos
2025-06-10 different port
2025-06-11 use macros instead of numbers, organization
2025-06-11 ADC macros, machine and can_app freqs. safety check
2025-06-11 PRINT and LED macros
2025-06-11 use new macros from conf and header file
2025-06-19 small changes in print infos and its vars
2025-06-19 formatting and organization
2025-06-19 Use MIC19 pumps msg, pump1 changes steering sensitivity by changin Kp
2025-10-15 taking notes of pot values and readings
2025-10-15 standard should be defined PRINT_INFOS
